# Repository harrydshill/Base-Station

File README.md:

## Base-Station
PCB for an RTL-SDR basestation I am working on. Ideal is to have an SDR with QRH antenna for talking to NOAA satellites. An Arduino UNO Q is used to allow for linux - makes life easier with using GPredict and such to track the satellite. 

## PCB Features

# Main PCB
- RS485 (for controlling PELCO mount to rotate antenna to track satellite)
- USB hub (to split the single USB-C port of the UNO Q into two ports)
- Temperature and current sense
- PoL converters for each USB port

# LDO PCB 
- Ultra high performance inline LDO board to condition the power supply for the RTL-SDR

##Status
Wip 😱

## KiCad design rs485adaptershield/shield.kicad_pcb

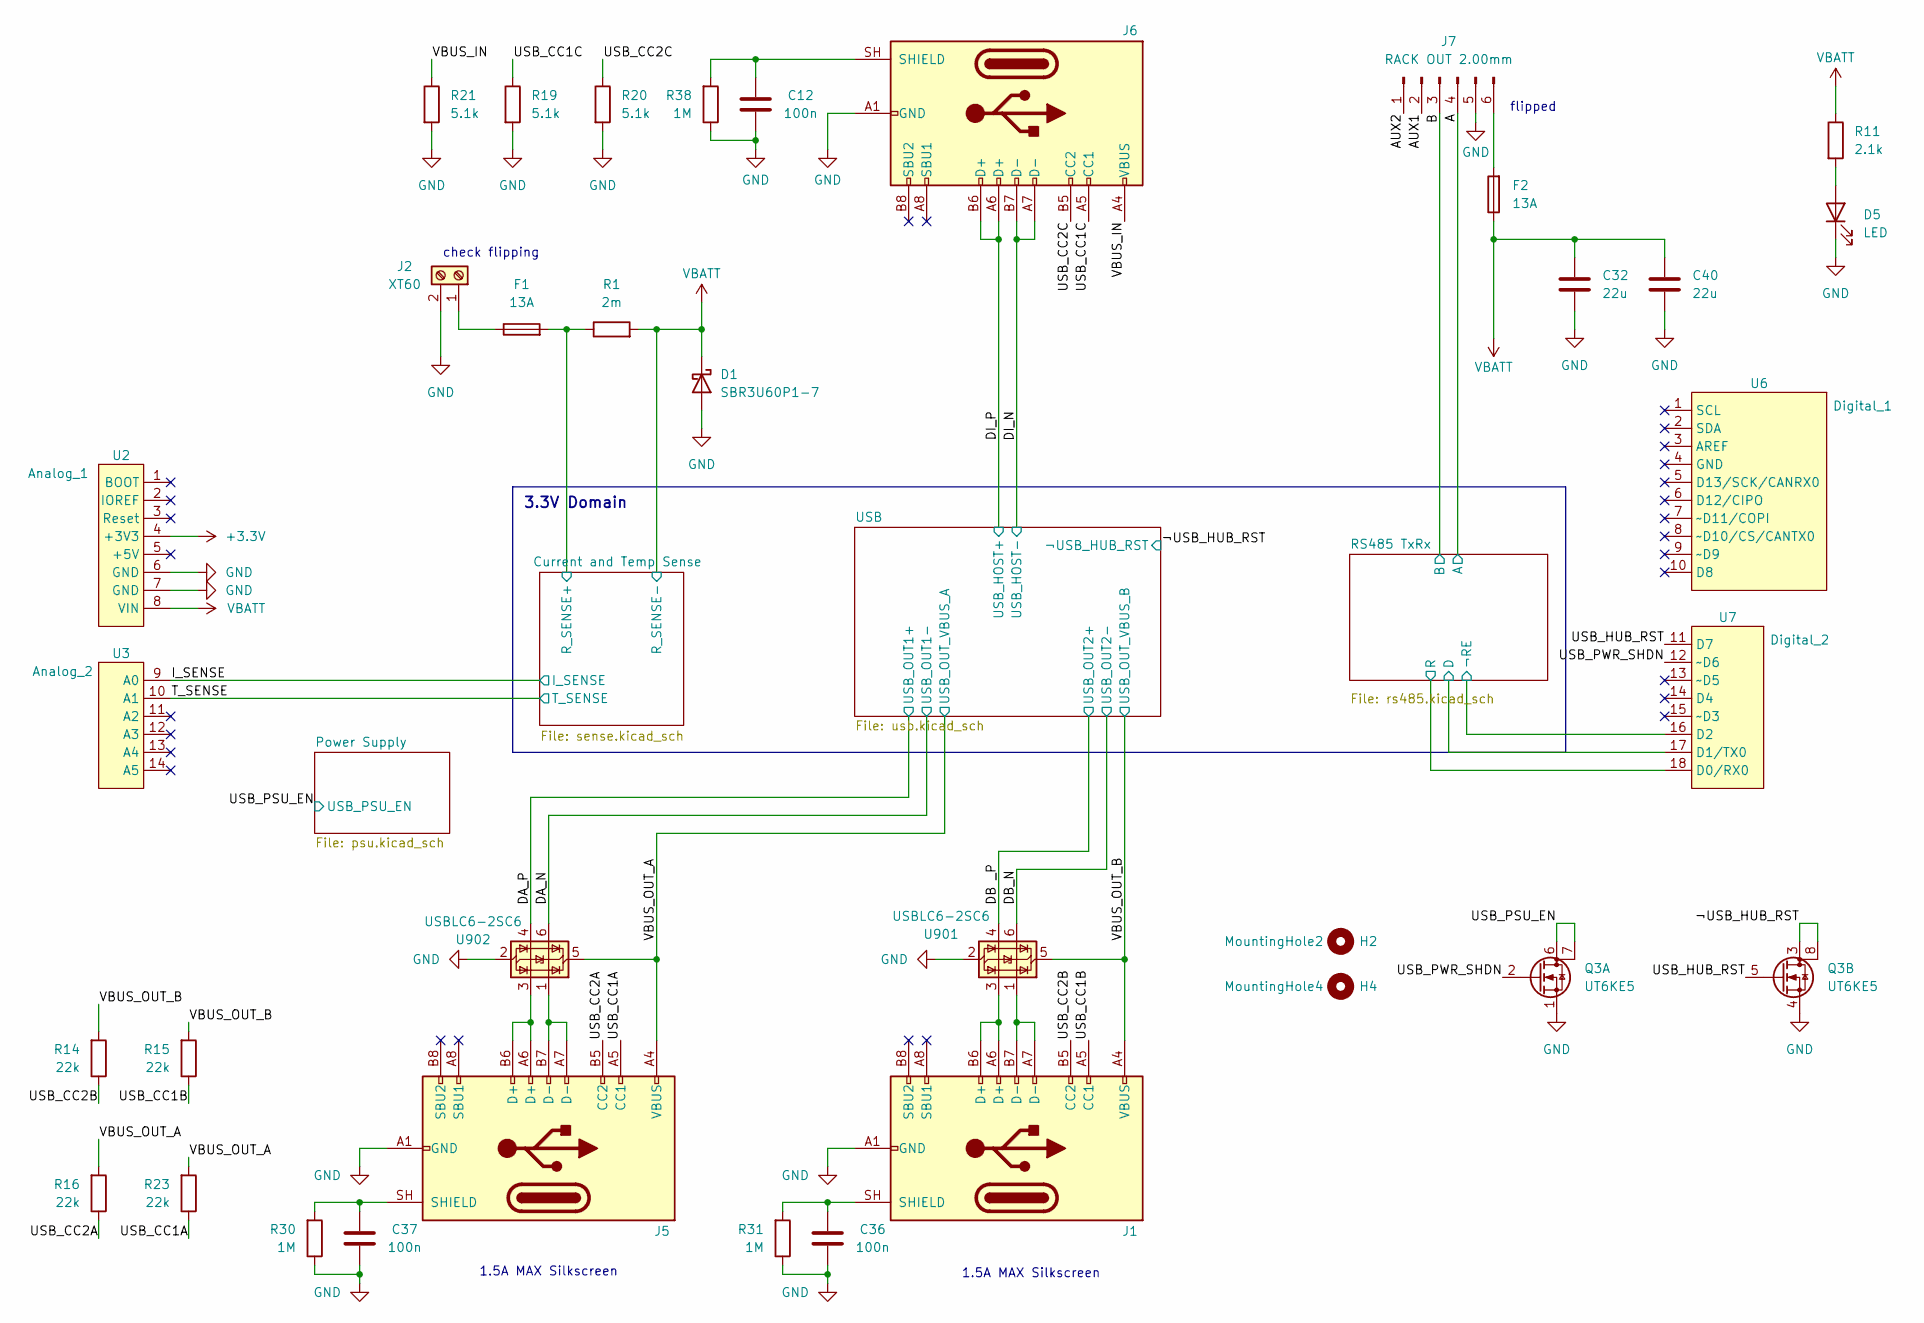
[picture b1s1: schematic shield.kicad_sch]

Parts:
C12, C36, C37: 100n; C_0402_1005Metric
C32, C40: 22u; C_1210_3225Metric
D1: SBR3U60P1-7; D_PowerDI-123; Mouser Part Number 621-SBR3U60P1-7
D5: LED; LED_0603_1608Metric
F1, F2: 13A; Fuse_1812_4532Metric
H2: MountingHole2; Arduino_MountingHole
H4: MountingHole4; Arduino_MountingHole
J1, J5, J6: USB_C_Receptacle_GCT_USB4110
J2: XT60; AMASS_XT60PW-F_1x02_P7.20mm_Horizontal
J7: RACK OUT 2.00mm; PinHeader_1x06_P2.00mm_Vertical
Q3: UT6KE5; UT6KE5TCR
R1: 2m; R_0603_1608Metric
R11: 2.1k; R_0603_1608Metric
R14, R15, R16, R23: 22k; R_0402_1005Metric
R19, R20, R21: 5.1k; R_0402_1005Metric
R30, R31, R38: 1M; R_0402_1005Metric
U2: Analog_1; Arduino_PinSocket_1x08_P2.54mm_Vertical
U3: Analog_2; Arduino_PinSocket_1x06_P2.54mm_Vertical
U6: Digital_1; Arduino_PinSocket_1x10_P2.54mm_Vertical
U7: Digital_2; Arduino_PinSocket_1x08_P2.54mm_Vertical
U901, U902: USBLC6-2SC6; SOT-23-6

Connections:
+3.3V: U2.4 (+3V3); also elsewhere on the board
/A: J7.4; also elsewhere on the board
/AUX1: J7.2
/AUX2: J7.1
/B: J7.3; also elsewhere on the board
/Current and Temp Sense/R_SENSE+: F1.2, R1.1; also elsewhere on the board
/DA_N: U902.6 (I/O1); also elsewhere on the board
/DA_P: U902.4 (I/O2); also elsewhere on the board
/DB _P: U901.4 (I/O2); also elsewhere on the board
/DB_N: U901.6 (I/O1); also elsewhere on the board
/DI_N: J6.A7 (D-), J6.B7 (D-); also elsewhere on the board
/DI_P: J6.A6 (D+), J6.B6 (D+); also elsewhere on the board
/I_SENSE: U3.9 (A0); also elsewhere on the board
/RS485 TxRx/D: U7.17 (D1/TX0); also elsewhere on the board
/RS485 TxRx/R: U7.18 (D0/RX0); also elsewhere on the board
/RS485 TxRx/¬RESET: U7.16 (D2); also elsewhere on the board
/T_SENSE: U3.10 (A1); also elsewhere on the board
/USB_CC1A: J5.A5 (CC1), R23.1
/USB_CC1B: J1.A5 (CC1), R15.1
/USB_CC1C: J6.A5 (CC1), R19.1
/USB_CC2A: J5.B5 (CC2), R16.1
/USB_CC2B: J1.B5 (CC2), R14.1
/USB_CC2C: J6.B5 (CC2), R20.1
/USB_HUB_RST: Q3.5 (G), U7.11 (D7)
/USB_PSU_EN: Q3.6 (D), Q3.7 (D); also elsewhere on the board
/USB_PWR_SHDN: Q3.2 (G), U7.12 (~D6)
/VBUS_IN: J6.A4 (VBUS), J6.A9 (VBUS), J6.B4 (VBUS), J6.B9 (VBUS), R21.1
/VBUS_OUT_A: J5.A4 (VBUS), J5.A9 (VBUS), J5.B4 (VBUS), J5.B9 (VBUS), R16.2, R23.2, U902.5 (VBUS); also elsewhere on the board
/VBUS_OUT_B: J1.A4 (VBUS), J1.A9 (VBUS), J1.B4 (VBUS), J1.B9 (VBUS), R14.2, R15.2, U901.5 (VBUS); also elsewhere on the board
/¬USB_HUB_RST: Q3.3 (D), Q3.8 (D); also elsewhere on the board
GND: C12.2, C32.2, C36.2, C37.2, C40.2, D1.2 (A), D5.1 (K), J1.A1 (GND), J1.A12 (GND), J1.B1 (GND), J1.B12 (GND), J2.2, J5.A1 (GND), J5.A12 (GND), J5.B1 (GND), J5.B12 (GND), J6.A1 (GND), J6.A12 (GND), J6.B1 (GND), J6.B12 (GND), J7.5, Q3.1 (S), Q3.4 (S), R19.2, R20.2, R21.2, R30.1, R31.1, R38.1, U2.6 (GND), U2.7 (GND), U901.2 (GND), U902.2 (GND); also elsewhere on the board
unnamed: D5.2 (A), R11.2
unnamed: J1.A6 (D+), J1.B6 (D+), U901.3 (I/O2)
unnamed: J1.A7 (D-), J1.B7 (D-), U901.1 (I/O1)
unnamed: C36.1, J1.SH (SHIELD), R31.2
unnamed: F1.1, J2.1
unnamed: J5.A6 (D+), J5.B6 (D+), U902.3 (I/O2)
unnamed: J5.A7 (D-), J5.B7 (D-), U902.1 (I/O1)
unnamed: C37.1, J5.SH (SHIELD), R30.2
unnamed: C12.1, J6.SH (SHIELD), R38.2
unnamed: F2.2, J7.6
VBATT: C32.1, C40.1, D1.1 (K), F2.1, R1.2, R11.1, U2.8 (VIN); also elsewhere on the board

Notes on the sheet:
flipped
1.5A MAX Silkscreen
3.3V Domain
check flipping

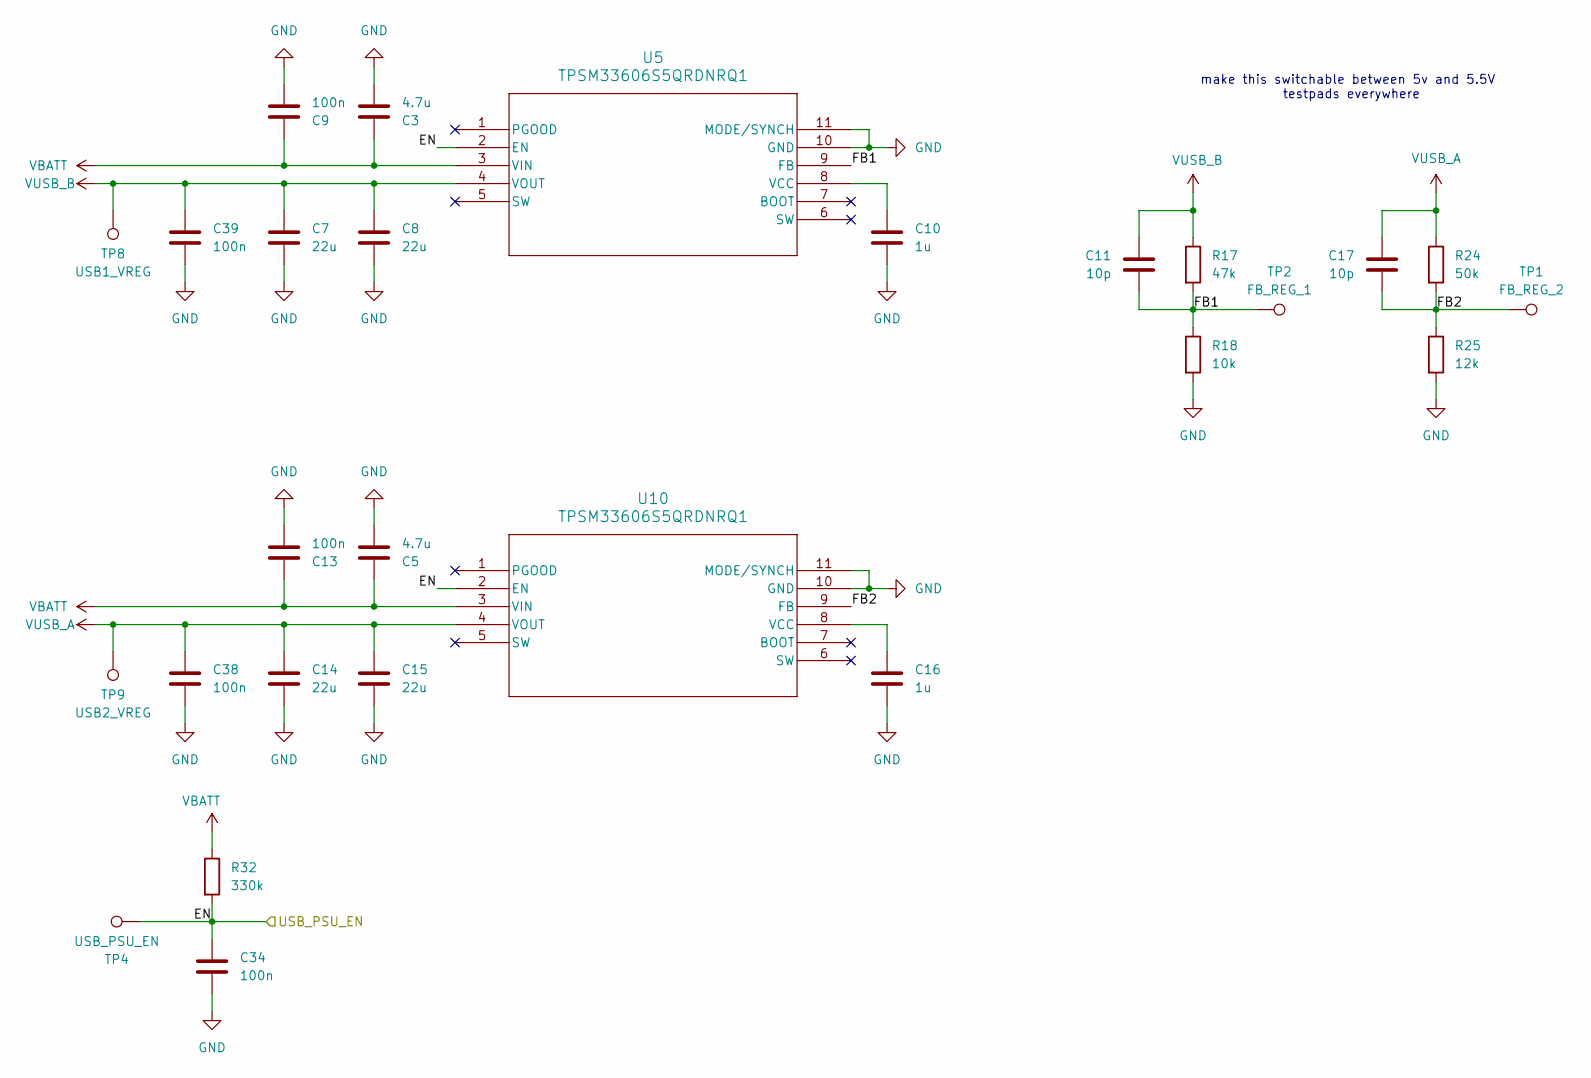
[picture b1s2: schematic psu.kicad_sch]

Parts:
C3, C5: 4.7u; C_0805_2012Metric
C7, C8, C14, C15: 22u; C_1210_3225Metric
C9, C13, C34, C38, C39: 100n; C_0402_1005Metric
C10, C16: 1u; C_0603_1608Metric
C11, C17: 10p; C_0402_1005Metric
R17: 47k; R_0402_1005Metric
R18: 10k; R_0402_1005Metric
R24: 50k; R_0402_1005Metric
R25: 12k; R_0402_1005Metric
R32: 330k; R_0402_1005Metric
TP1: FB_REG_2; TestPoint_Pad_D1.0mm
TP2: FB_REG_1; TestPoint_Pad_D1.0mm
TP4: USB_PSU_EN; TestPoint_Pad_D1.0mm
TP8: USB1_VREG; TestPoint_Pad_D1.0mm
TP9: USB2_VREG; TestPoint_Pad_D1.0mm
U5, U10: TPSM33606S5QRDNRQ1; RDN0011A_TEX_NEW

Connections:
/Power Supply/FB1: C11.2, R17.2, R18.1, TP2.1 (1_1), U5.9 (FB)
/Power Supply/FB2: C17.2, R24.2, R25.1, TP1.1 (1_1), U10.9 (FB)
/USB_PSU_EN: C34.2, R32.2, TP4.1 (1_1), U5.2 (EN), U10.2 (EN); also elsewhere on the board
GND: C3.2, C5.2, C7.2, C8.2, C9.2, C10.2, C13.2, C14.2, C15.2, C16.2, C34.1, C38.2, C39.2, R18.2, R25.2, U5.10 (GND), U5.11 (MODE/SYNCH), U10.10 (GND), U10.11 (MODE/SYNCH); also elsewhere on the board
unnamed: C10.1, U5.8 (VCC)
unnamed: C16.1, U10.8 (VCC)
VBATT: C3.1, C5.1, C9.1, C13.1, R32.1, U5.3 (VIN), U10.3 (VIN); also elsewhere on the board
VUSB_A: C14.1, C15.1, C17.1, C38.1, R24.1, TP9.1 (1_1), U10.4 (VOUT); also elsewhere on the board
VUSB_B: C7.1, C8.1, C11.1, C39.1, R17.1, TP8.1 (1_1), U5.4 (VOUT); also elsewhere on the board

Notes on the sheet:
make this switchable between 5v and 5.5V
testpads everywhere

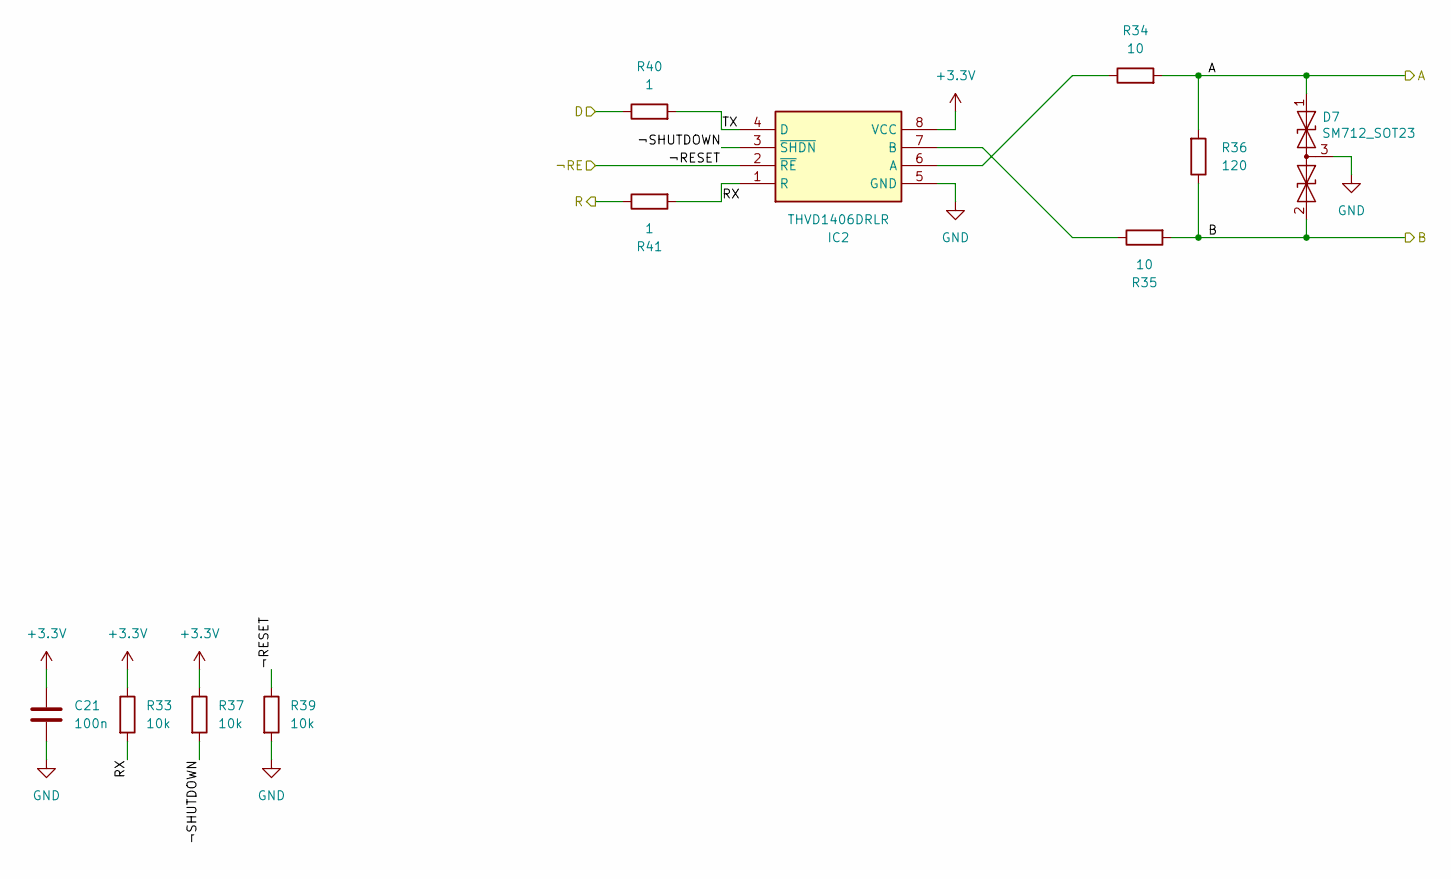
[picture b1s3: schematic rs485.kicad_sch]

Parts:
C21: 100n; C_0402_1005Metric
D7: SM712_SOT23; SOT-23
IC2: THVD1406DRLR; SOT-23-8; Mouser Part Number 595-THVD1406DRLR
R33, R37, R39: 10k; R_0402_1005Metric
R34, R35: 10; R_0603_1608Metric
R36: 120; R_0805_2012Metric
R40, R41: 1; R_0603_1608Metric

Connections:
+3.3V: C21.2, IC2.8 (VCC), R33.1, R37.1; also elsewhere on the board
/A: D7.1 (A1), R34.2, R36.2; also elsewhere on the board
/B: D7.2 (A2), R35.2, R36.1; also elsewhere on the board
/RS485 TxRx/D: R40.1; also elsewhere on the board
/RS485 TxRx/R: R41.1; also elsewhere on the board
/RS485 TxRx/RX: IC2.1 (R), R33.2, R41.2
/RS485 TxRx/TX: IC2.4 (D), R40.2
/RS485 TxRx/¬RESET: IC2.2 (~RE), R39.1; also elsewhere on the board
/RS485 TxRx/¬SHUTDOWN: IC2.3 (~SHDN), R37.2
GND: C21.1, D7.3 (common), IC2.5 (GND), R39.2; also elsewhere on the board
unnamed: IC2.6 (A), R34.1
unnamed: IC2.7 (B), R35.1

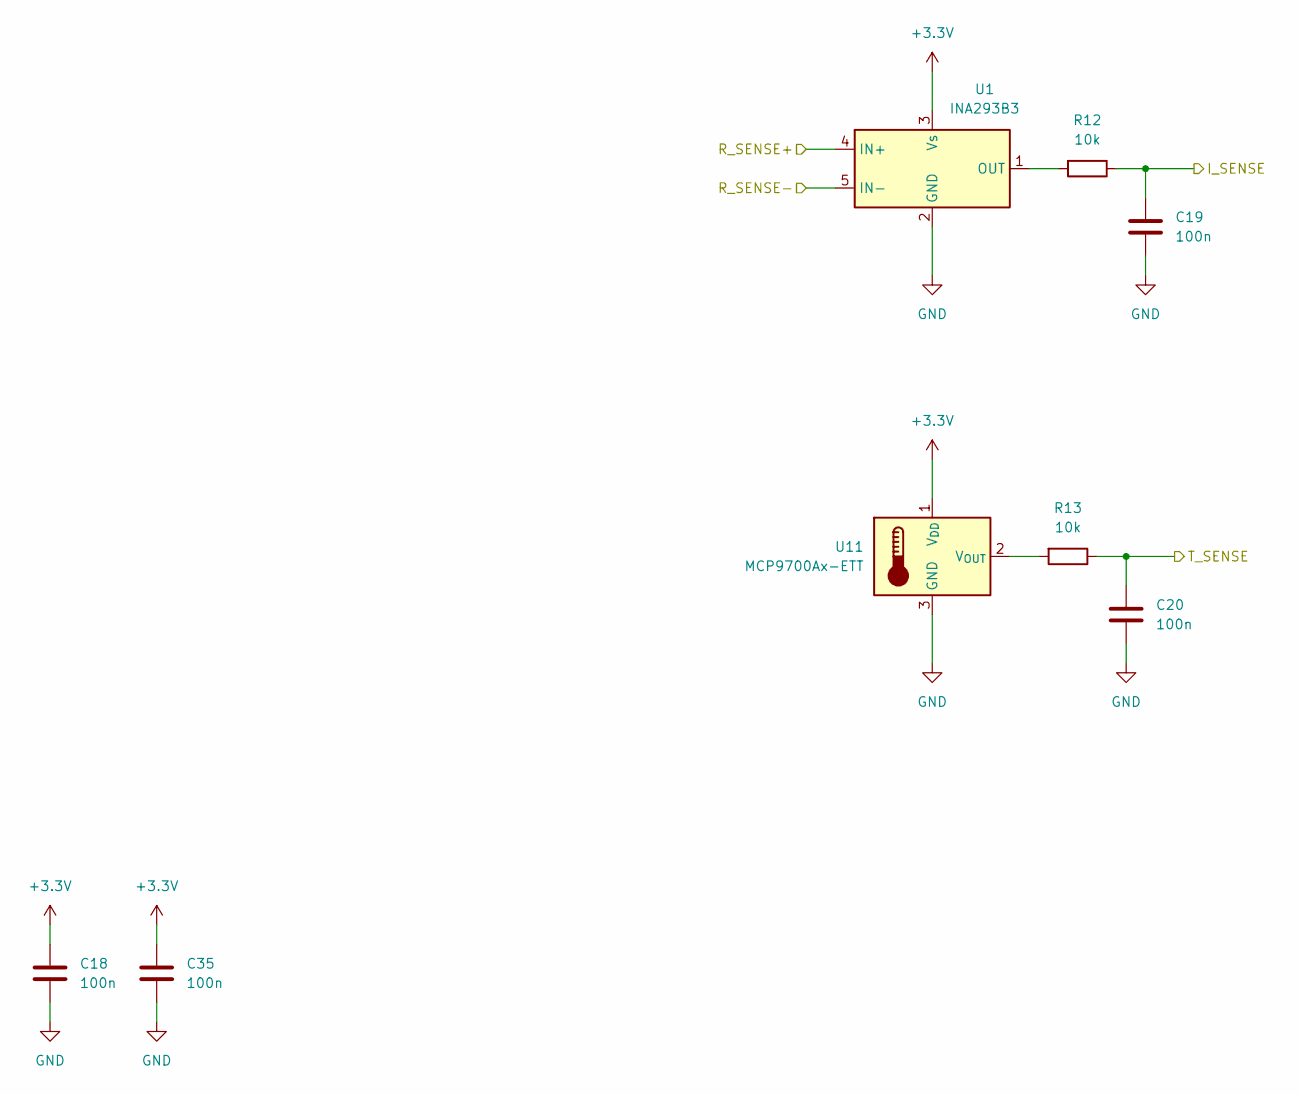
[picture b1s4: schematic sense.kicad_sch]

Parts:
C18, C19, C20, C35: 100n; C_0402_1005Metric
R12, R13: 10k; R_0402_1005Metric
U1: INA293B3; SOT-23-5
U11: MCP9700Ax-ETT; SOT-23

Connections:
+3.3V: C18.2, C35.2, U1.3 (Vs), U11.1 (V_{DD}); also elsewhere on the board
/Current and Temp Sense/R_SENSE+: U1.4 (IN+); also elsewhere on the board
/I_SENSE: C19.1, R12.1; also elsewhere on the board
/T_SENSE: C20.1, R13.1; also elsewhere on the board
GND: C18.1, C19.2, C20.2, C35.1, U1.2 (GND), U11.3 (GND); also elsewhere on the board
unnamed: R12.2, U1.1 (OUT)
unnamed: R13.2, U11.2 (V_{OUT})
VBATT: U1.5 (IN-); also elsewhere on the board

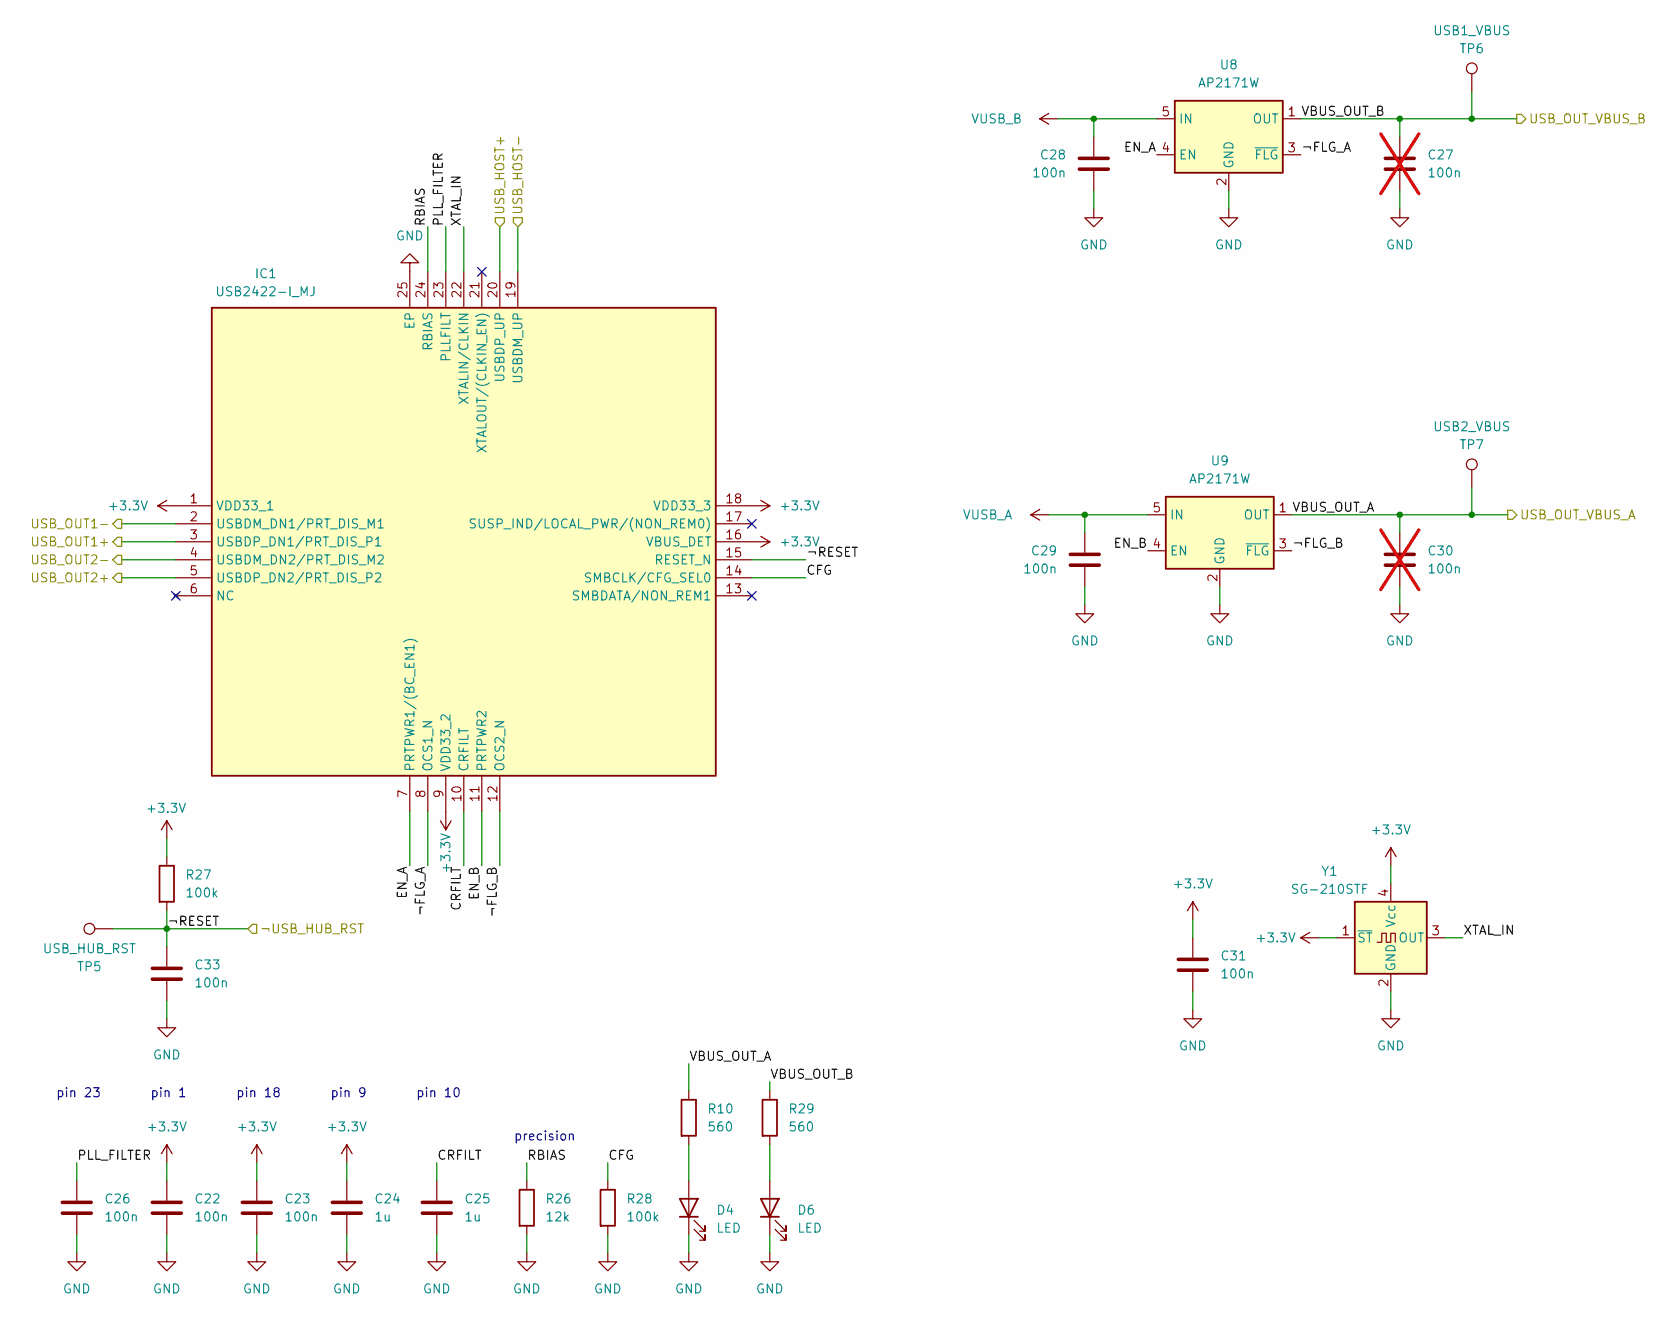
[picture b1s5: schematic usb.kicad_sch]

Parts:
C22, C23, C26, C28, C29, C31, C33: 100n; C_0402_1005Metric
C24, C25: 1u; C_0402_1005Metric
C27, C30: 100n; C_0402_1005Metric; not fitted
D4, D6: LED; LED_0603_1608Metric
IC1: USB2422-I_MJ; QFN-24-1EP_4x4mm_P0.5mm_EP2.5x2.5mm; Mouser Part Number 579-USB2422-I/MJ
R10, R29: 560; R_0402_1005Metric
R26: 12k; R_0402_1005Metric
R27, R28: 100k; R_0402_1005Metric
TP5: USB_HUB_RST; TestPoint_Pad_D1.0mm
TP6: USB1_VBUS; TestPoint_Pad_D1.0mm
TP7: USB2_VBUS; TestPoint_Pad_D1.0mm
U8, U9: AP2171W; SOT-23-5
Y1: SG-210STF; Oscillator_SMD_SeikoEpson_SG210-4Pin_2.5x2.0mm

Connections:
+3.3V: C22.2, C23.2, C24.2, C31.2, IC1.1 (VDD33_1), IC1.9 (VDD33_2), IC1.16 (VBUS_DET), IC1.18 (VDD33_3), R27.1, Y1.1 (~ST), Y1.4 (Vcc); also elsewhere on the board
/DA_N: IC1.2 (USBDM_DN1/PRT_DIS_M1); also elsewhere on the board
/DA_P: IC1.3 (USBDP_DN1/PRT_DIS_P1); also elsewhere on the board
/DB _P: IC1.5 (USBDP_DN2/PRT_DIS_P2); also elsewhere on the board
/DB_N: IC1.4 (USBDM_DN2/PRT_DIS_M2); also elsewhere on the board
/DI_N: IC1.19 (USBDM_UP); also elsewhere on the board
/DI_P: IC1.20 (USBDP_UP); also elsewhere on the board
/USB/CFG: IC1.14 (SMBCLK/CFG_SEL0), R28.1
/USB/CRFILT: C25.2, IC1.10 (CRFILT)
/USB/EN_A: IC1.7 (PRTPWR1/(BC_EN1)), U8.4 (EN)
/USB/EN_B: IC1.11 (PRTPWR2), U9.4 (EN)
/USB/PLL_FILTER: C26.2, IC1.23 (PLLFILT)
/USB/RBIAS: IC1.24 (RBIAS), R26.1
/USB/XTAL_IN: IC1.22 (XTALIN/CLKIN), Y1.3 (OUT)
/USB/¬FLG_A: IC1.8 (OCS1_N), U8.3 (~FLG)
/USB/¬FLG_B: IC1.12 (OCS2_N), U9.3 (~FLG)
/VBUS_OUT_A: C30.2, R10.1, TP7.1 (1_1), U9.1 (OUT); also elsewhere on the board
/VBUS_OUT_B: C27.2, R29.1, TP6.1 (1_1), U8.1 (OUT); also elsewhere on the board
/¬USB_HUB_RST: C33.2, IC1.15 (RESET_N), R27.2, TP5.1 (1_1); also elsewhere on the board
GND: C22.1, C23.1, C24.1, C25.1, C26.1, C27.1, C28.1, C29.1, C30.1, C31.1, C33.1, D4.1 (K), D6.1 (K), IC1.25 (EP), R26.2, R28.2, U8.2 (GND), U9.2 (GND), Y1.2 (GND); also elsewhere on the board
unnamed: D4.2 (A), R10.2
unnamed: D6.2 (A), R29.2
VUSB_A: C29.2, U9.5 (IN); also elsewhere on the board
VUSB_B: C28.2, U8.5 (IN); also elsewhere on the board

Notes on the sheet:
pin 10
pin 18
pin 9
pin 23
precision
pin 1

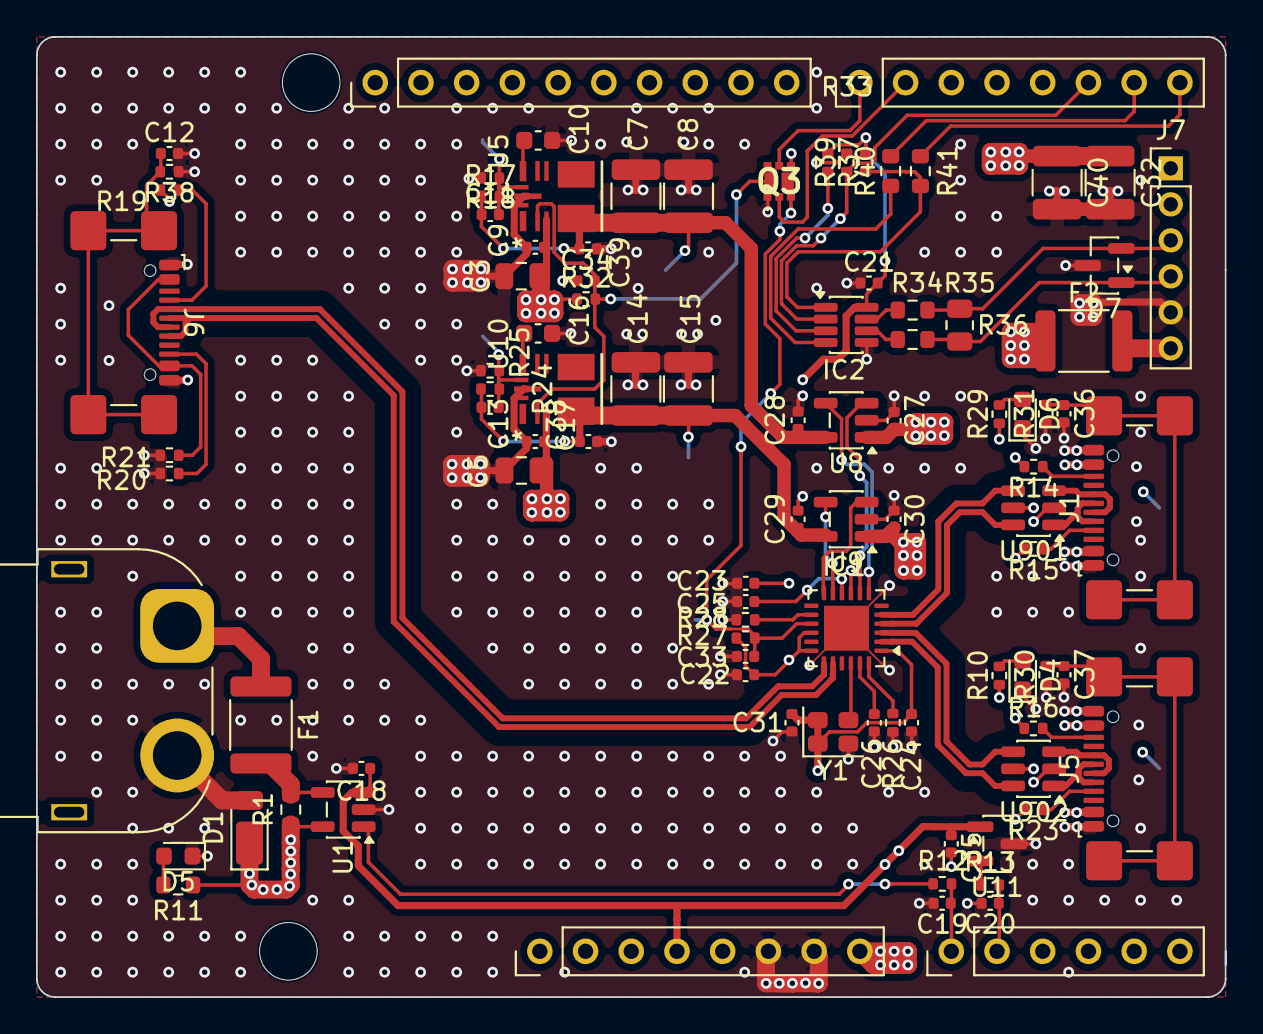
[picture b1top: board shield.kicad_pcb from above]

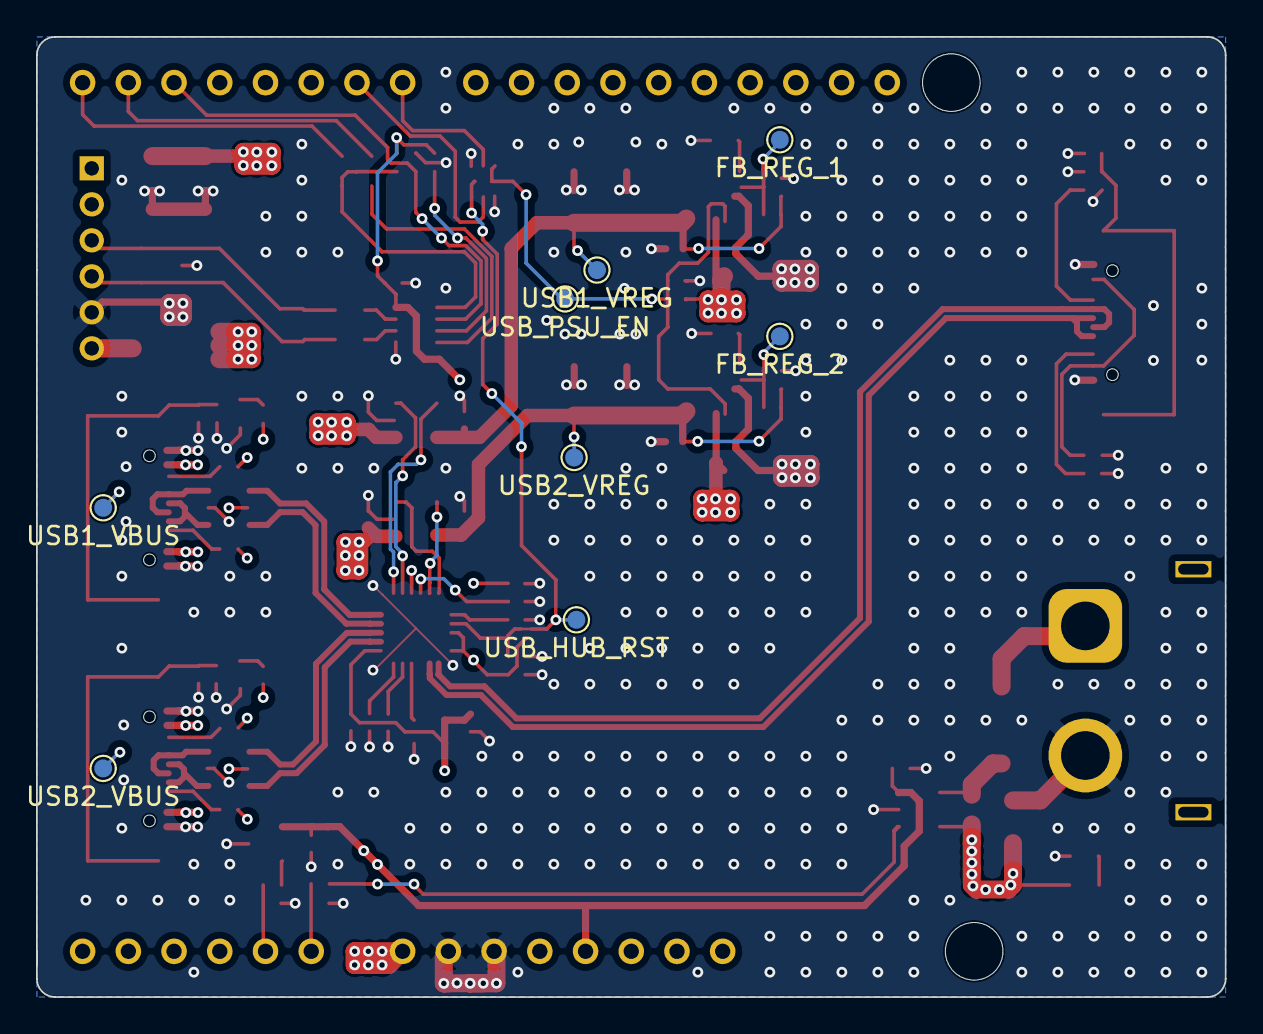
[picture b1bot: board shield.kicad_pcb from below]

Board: 4 copper layers, 66.0 x 53.3 mm, 106 parts (8 on the bottom side), 64 nets.

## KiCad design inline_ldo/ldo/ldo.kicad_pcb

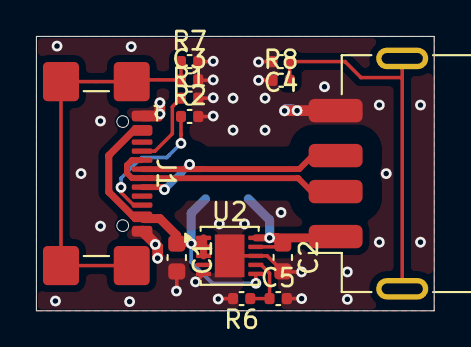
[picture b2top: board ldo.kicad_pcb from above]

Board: 4 copper layers, 22.1 x 15.2 mm, 14 parts (1 on the bottom side), 10 nets.

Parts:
C1, C2: 10u; C_0603_1608Metric
C3, C4: 100n; C_0402_1005Metric
C5: 470n; C_0402_1005Metric
D1: SBR3U60P1-7; D_PowerDI-123
J1: USB_C_Receptacle_GCT_USB4110
J2: USB_A; USB_A_Receptacle_GCT_USB1046
R1, R2: 5.1k; C_0402_1005Metric
R6: 5k; C_0402_1005Metric
R7, R8: 1M; C_0402_1005Metric
U2: LT3045xDD; DFN-10-1EP_3x3mm_P0.5mm_EP1.65x2.38mm

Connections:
5V: C2.1, D1.1 (K), J2.1 (VBUS), U2.9 (OUTS), U2.10 (OUT)
/D+: J1.A6 (D+), J1.B6 (D+), J2.3 (D+)
/D-: J1.A7 (D-), J1.B7 (D-), J2.2 (D-)
/USB_CC1: J1.A5 (CC1), R1.1
/USB_CC2: J1.B5 (CC2), R2.1
GND: C1.2, C2.2, C3.2, C4.2, C5.2, J1.A1 (GND), J1.A12 (GND), J1.B1 (GND), J1.B12 (GND), J2.4 (GND), R1.2, R2.2, R6.2, R7.2, R8.1, U2.5 (ILIM), U2.8 (GND), U2.11 (GND)
unnamed: C3.1, J1.SH (SHIELD), R7.1
unnamed: C4.1, R8.2
unnamed: C5.1, R6.1, U2.7 (SET)
VIN: C1.1, D1.2 (A), J1.A4 (VBUS), J1.A9 (VBUS), J1.B4 (VBUS), J1.B9 (VBUS), U2.1 (IN), U2.2 (IN), U2.3 (EN/UV), U2.6 (PGFB)

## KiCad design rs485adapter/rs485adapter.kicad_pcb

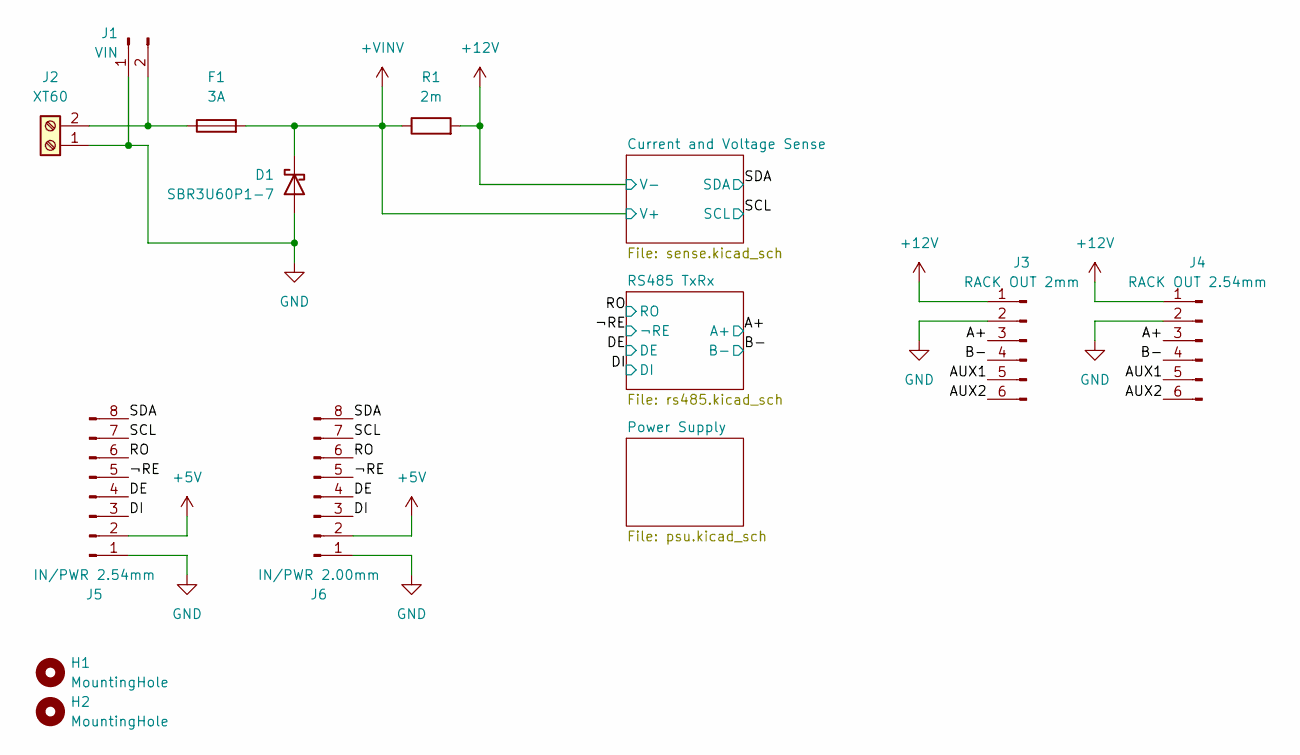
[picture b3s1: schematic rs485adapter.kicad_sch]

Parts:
D1: SBR3U60P1-7; D_PowerDI-123; Mouser Part Number 621-SBR3U60P1-7
F1: 3A; Fuse_1812_4532Metric
H1, H2: MountingHole; MountingHole_2.2mm_M2
J1: VIN; PinHeader_1x02_P2.54mm_Vertical
J2: XT60; AMASS_XT60PW-F_1x02_P7.20mm_Horizontal
J3: RACK OUT 2mm; PinHeader_1x06_P2.00mm_Vertical
J4: RACK OUT 2.54mm; PinHeader_1x06_P2.54mm_Vertical
J5: IN/PWR 2.54mm; PinHeader_1x08_P2.54mm_Vertical
J6: IN/PWR 2.00mm; PinHeader_1x08_P2.00mm_Vertical
R1: 2m; R_0805_2012Metric

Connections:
+5V: J5.2, J6.2; also elsewhere on the board
+12V: J3.1, J4.1, R1.2; also elsewhere on the board
+VINV: D1.1 (K), F1.2, R1.1; also elsewhere on the board
/A+: J3.3, J4.3; also elsewhere on the board
/AUX1: J3.5, J4.5
/AUX2: J3.6, J4.6
/B-: J3.4, J4.4; also elsewhere on the board
/DE: J5.4, J6.4; also elsewhere on the board
/DI: J5.3, J6.3; also elsewhere on the board
/RO: J5.6, J6.6; also elsewhere on the board
/SCL: J5.7, J6.7; also elsewhere on the board
/SDA: J5.8, J6.8; also elsewhere on the board
/¬RE: J5.5, J6.5; also elsewhere on the board
GND: D1.2 (A), J1.1, J2.1, J3.2, J4.2, J5.1, J6.1; also elsewhere on the board
unnamed: F1.1, J1.2, J2.2

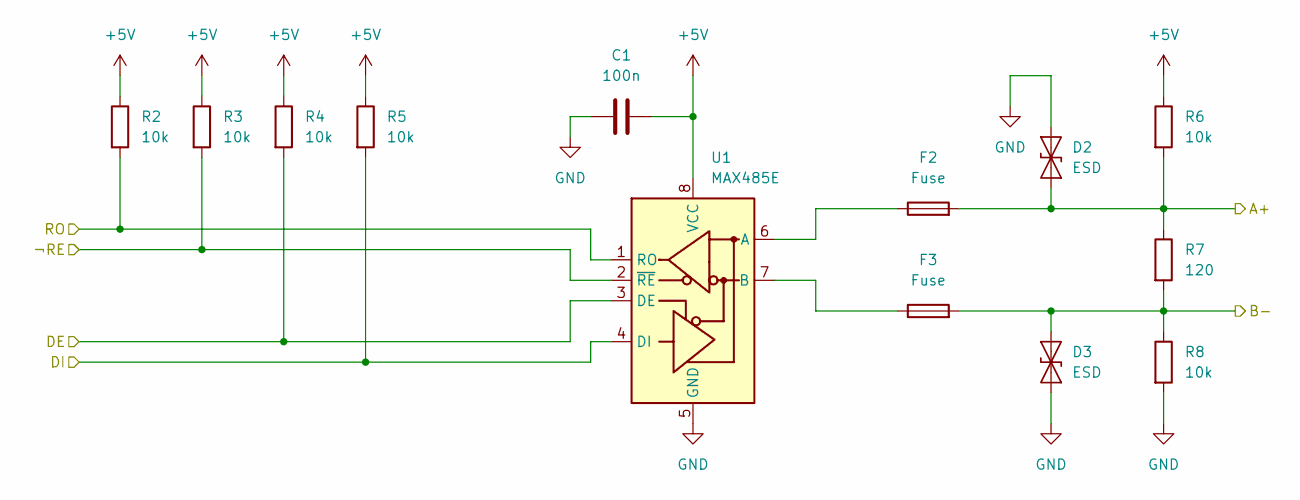
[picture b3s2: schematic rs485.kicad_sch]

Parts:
C1: 100n; C_0805_2012Metric
D2, D3: ESD; D_SMA
F2, F3: Fuse; Fuse_1812_4532Metric
R2, R3, R4, R5, R6, R8: 10k; R_0805_2012Metric
R7: 120; R_0805_2012Metric
U1: MAX485E; SOIC-8_3.9x4.9mm_P1.27mm

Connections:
+5V: C1.2, R2.1, R3.1, R4.1, R5.1, R6.1, U1.8 (VCC); also elsewhere on the board
/A+: D2.2 (A2), F2.2, R6.2, R7.1; also elsewhere on the board
/B-: D3.2 (A2), F3.2, R7.2, R8.1; also elsewhere on the board
/DE: R4.2, U1.3 (DE); also elsewhere on the board
/DI: R5.2, U1.4 (DI); also elsewhere on the board
/RO: R2.2, U1.1 (RO); also elsewhere on the board
/¬RE: R3.2, U1.2 (~RE); also elsewhere on the board
GND: C1.1, D2.1 (A1), D3.1 (A1), R8.2, U1.5 (GND); also elsewhere on the board
unnamed: F2.1, U1.6 (A)
unnamed: F3.1, U1.7 (B)

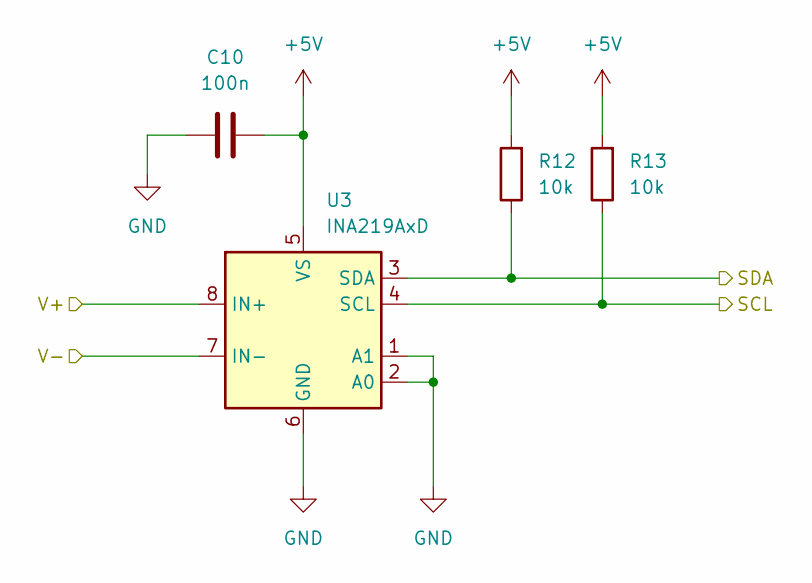
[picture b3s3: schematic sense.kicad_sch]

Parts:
C10: 100n; C_0805_2012Metric
R12, R13: 10k; R_0805_2012Metric
U3: INA219AxD; SOIC-8_3.9x4.9mm_P1.27mm

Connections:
+5V: C10.2, R12.2, R13.2, U3.5 (VS); also elsewhere on the board
+12V: U3.7 (IN-); also elsewhere on the board
+VINV: U3.8 (IN+); also elsewhere on the board
/SCL: R13.1, U3.4 (SCL); also elsewhere on the board
/SDA: R12.1, U3.3 (SDA); also elsewhere on the board
GND: C10.1, U3.1 (A1), U3.2 (A0), U3.6 (GND); also elsewhere on the board

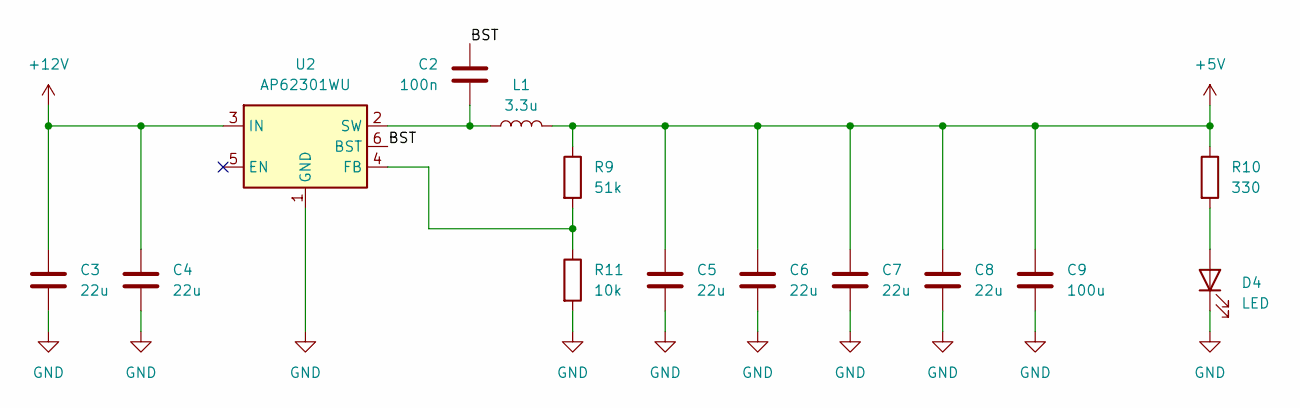
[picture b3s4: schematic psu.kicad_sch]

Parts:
C2: 100n; C_0805_2012Metric
C3, C4, C5, C6, C7, C8: 22u; C_1210_3225Metric
C9: 100u; CP_Elec_5x3.9
D4: LED; LED_0805_2012Metric
L1: 3.3u; L_Cenker_CKCS4030
R9: 51k; R_0805_2012Metric
R10: 330; R_0805_2012Metric
R11: 10k; R_0805_2012Metric
U2: AP62301WU; TSOT-23-6

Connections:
+5V: C5.1, C6.1, C7.1, C8.1, C9.1, L1.2, R9.1, R10.1; also elsewhere on the board
+12V: C3.1, C4.1, U2.3 (IN); also elsewhere on the board
/Power Supply/BST: C2.1, U2.6 (BST)
GND: C3.2, C4.2, C5.2, C6.2, C7.2, C8.2, C9.2, D4.1 (K), R11.2, U2.1 (GND); also elsewhere on the board
unnamed: D4.2 (A), R10.2
unnamed: R9.2, R11.1, U2.4 (FB)
unnamed: C2.2, L1.1, U2.2 (SW)
